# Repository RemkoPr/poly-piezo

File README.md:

# PolyPiezo

This repo contains the PCB design files for the wireless, modular, flexible piezoresistive skin sensor described in [Conveying Emotions to Robots through Touch and Sound](https://arxiv.org/abs/2412.03300), Qiaoqiao Ren, Remko Proesmans, et al, [Best Paper award at ICSR2024](https://icsr2024.dk/index.php/paper-nominees-and-awards/). Please contact remko.proesmans@ugent.be if you'd like support with implementing the design.

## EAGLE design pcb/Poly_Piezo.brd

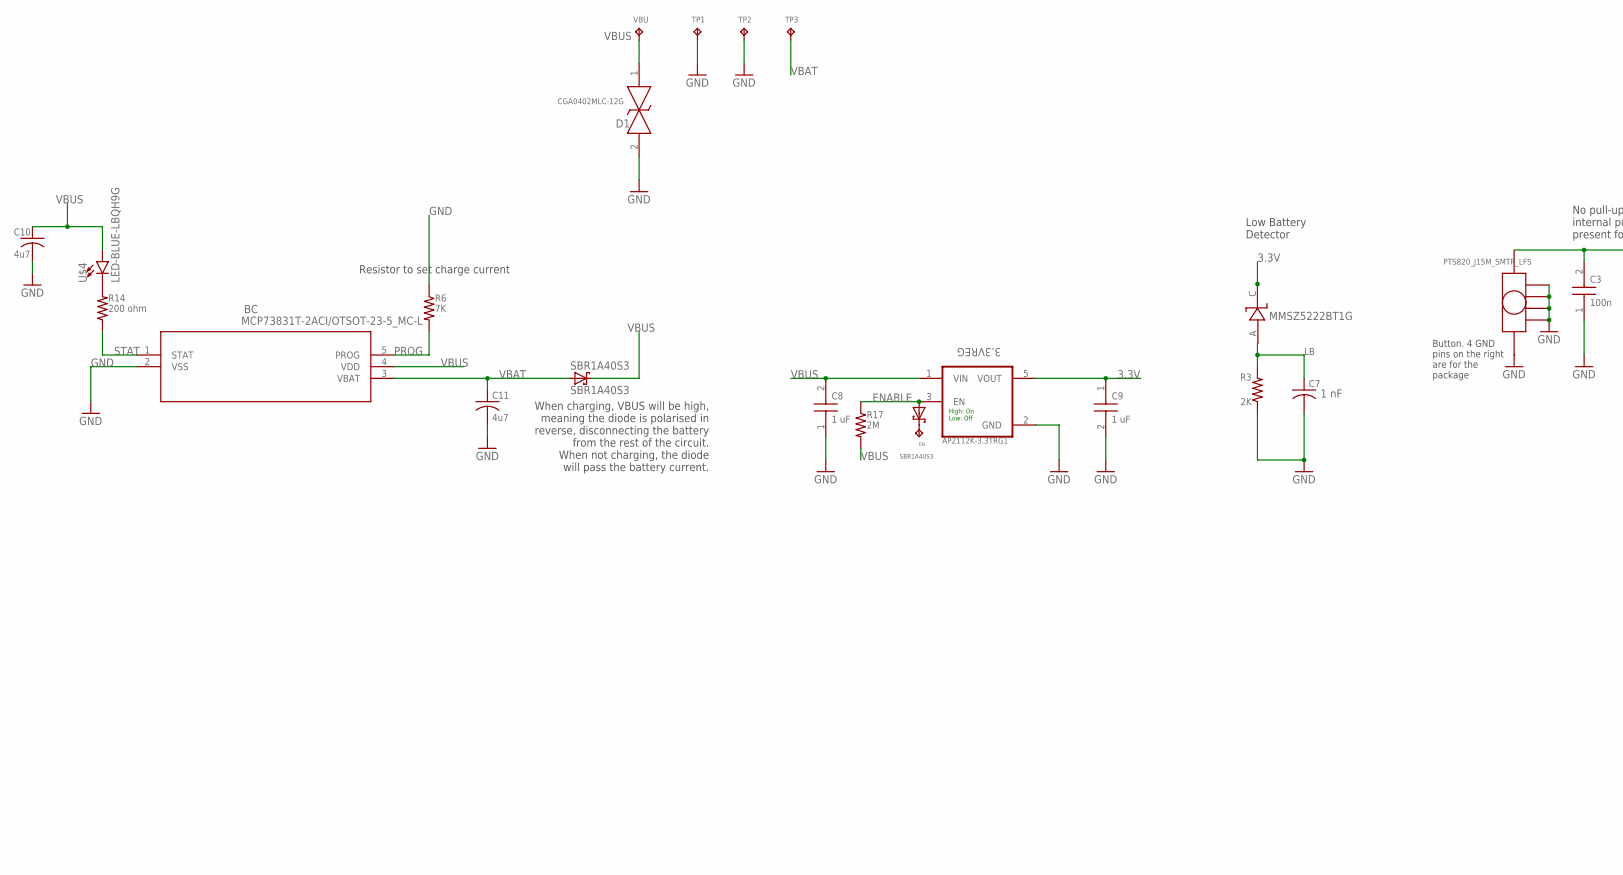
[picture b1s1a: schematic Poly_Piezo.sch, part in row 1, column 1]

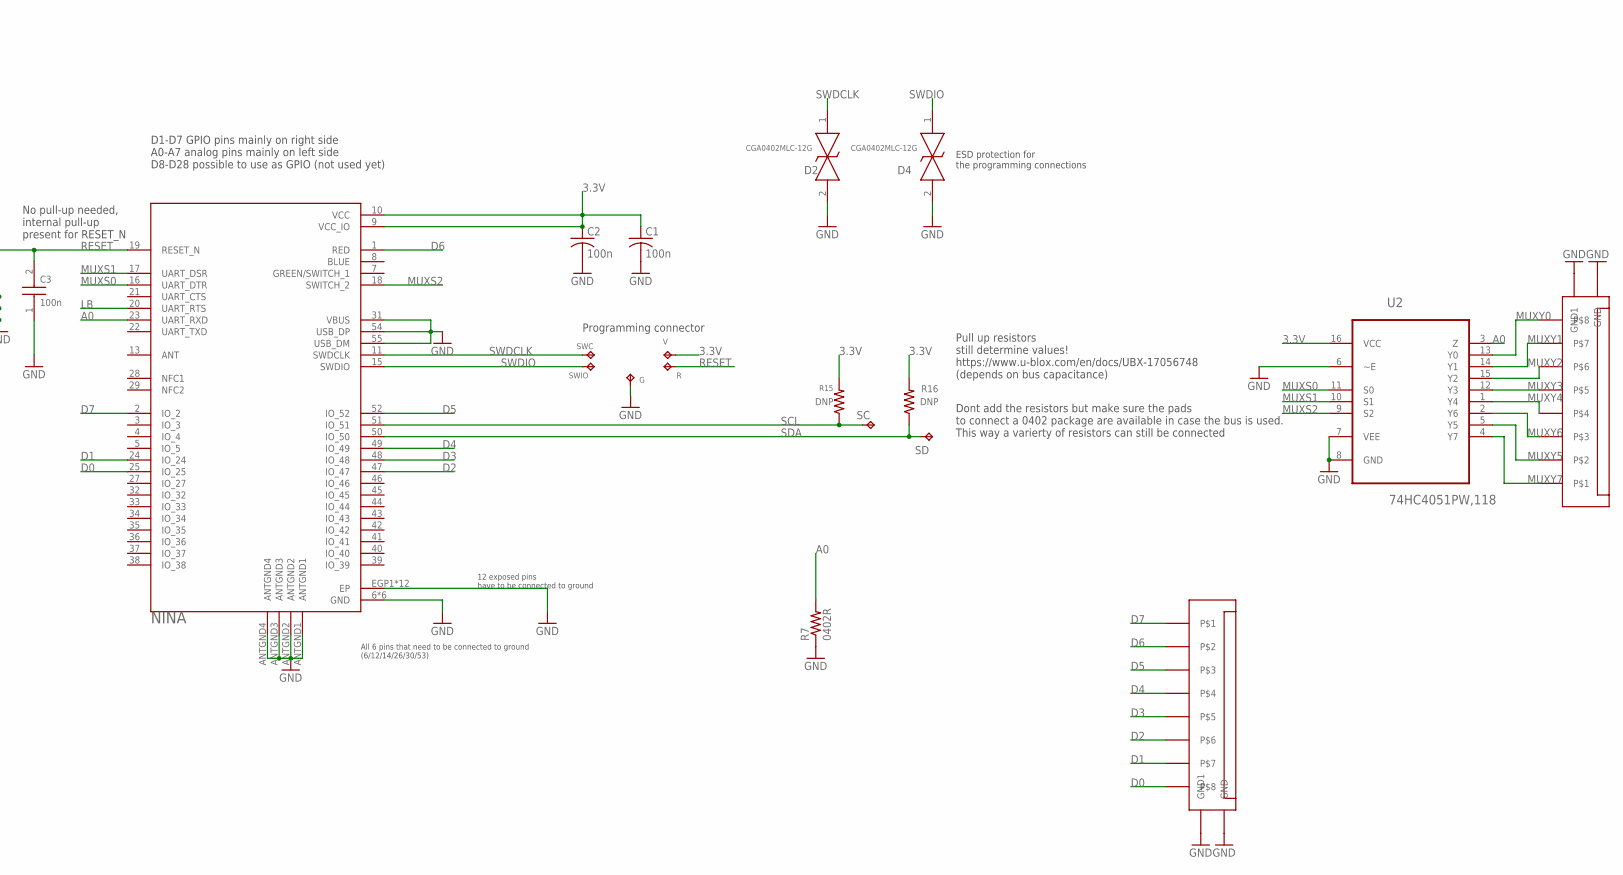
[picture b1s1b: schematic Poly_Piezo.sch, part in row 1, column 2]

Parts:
3.3VREG: AP2112K-3.3TRG1; SOT95P285X140-5N
BC: MCP73831T-2ACI/OTSOT-23-5_MC-L; SOT-23-5_MC-L
BUTTON: PTS820_J15M_SMTR_LFS; PTS820_J15
C1, C2: 100n; C0402
C3: 100n; CAPC1005X33N
C7: 1 nF; C0402
C8, C9: 1 uF; CAPC1005X33N
C10, C11: 4u7; C0402
D1, D2, D4: CGA0402MLC-12G; CGA0402MLC12G
EN: CUSTOM_HOLE1; CUSTOM_HOLE
G: TPB1,27; B1,27
MMSZ5222BT1G: MMSZ5222BT1G; SOD−123
R: TPB1,27; B1,27
R3: 2K; RESC1005X40N
R6: 7K; RESC1005X40N
R7: 0402R; RESC1005X40N
R14: 200 ohm; RESC1005X40N
R15, R16: DNP; RESC1005X40N
R17: 2M; RESC1005X40N
SBR1A40S3: SBR1A40S3; SOD323
SC: CUSTOM_HOLE1; CUSTOM_HOLE
SD: CUSTOM_HOLE1; CUSTOM_HOLE
SWC: TPB1,27; B1,27
SWIO: TPB1,27; B1,27
TP1, TP2, TP3: CUSTOM_HOLE1; CUSTOM_HOLE
U1: NINA; XCVR_NINA-B306
U2: 74HC4051PW,118; SOP65P640X110-16N
U$1, U$3: XF3M(1)-0815-1B
U$2: SBR1A40S3; SOD323
U$4: LED-BLUE-LBQH9G; LBQH9G-0402
V: TPB1,27; B1,27
VBU: CUSTOM_HOLE1; CUSTOM_HOLE

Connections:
3.3V: 3.3VREG.5 (VOUT), C1.1, C2.1, C9.1, MMSZ5222BT1G.C, R15.2, R16.2, U1.9 (VCC_IO), U1.10 (VCC), U2.16 (VCC), V.TP
A0: R7.2, U1.23 (UART_RXD), U2.3 (Z)
D0: U1.25 (IO_25), U$1.P$8
D1: U1.24 (IO_24), U$1.P$7
D2: U1.47 (IO_47), U$1.P$6
D3: U1.48 (IO_48), U$1.P$5
D4: U1.49 (IO_49), U$1.P$4
D5: U1.52 (IO_52), U$1.P$3
D6: U1.1 (RED), U$1.P$2
D7: U1.2 (IO_2), U$1.P$1
ENABLE: 3.3VREG.3 (EN), R17.1, U$2.A
GND: 3.3VREG.2 (GND), BC.2 (VSS), BUTTON.1, BUTTON.P$1, BUTTON.P$2, BUTTON.P$3, BUTTON.P$4, C1.2, C2.2, C3.1, C7.2, C8.1, C9.2, C10.2, C11.2, D1.2, D2.2, D4.2, G.TP, R3.1, R6.1, R7.1, TP1.P$1, TP2.P$1, U1.6 (GND), U1.12 (GND), U1.14 (GND), U1.26 (GND), U1.30 (GND), U1.31 (VBUS), U1.53 (GND), U1.54 (USB_DP), U1.55 (USB_DM), U1.ANTGND1, U1.ANTGND2, U1.ANTGND3, U1.ANTGND4, U1.EGP1 (EP), U1.EGP2 (EP), U1.EGP3 (EP), U1.EGP4 (EP), U1.EGP5 (EP), U1.EGP6 (EP), U1.EGP7 (EP), U1.EGP8 (EP), U1.EGP9 (EP), U1.EGP10 (EP), U1.EGP11 (EP), U1.EGP12 (EP), U2.6 (~E), U2.7 (VEE), U2.8 (GND), U$1.P$9 (GND1), U$1.P$10 (GND), U$3.P$9 (GND1), U$3.P$10 (GND)
LB: C7.1, MMSZ5222BT1G.A, R3.2, U1.20 (UART_RTS)
MUXS0: U1.16 (UART_DTR), U2.11 (S0)
MUXS1: U1.17 (UART_DSR), U2.10 (S1)
MUXS2: U1.18 (SWITCH_2), U2.9 (S2)
MUXY0: U2.13 (Y0), U$3.P$8
MUXY1: U2.14 (Y1), U$3.P$7
MUXY2: U2.15 (Y2), U$3.P$6
MUXY3: U2.12 (Y3), U$3.P$5
MUXY4: U2.1 (Y4), U$3.P$4
MUXY5: U2.5 (Y5), U$3.P$2
MUXY6: U2.2 (Y6), U$3.P$3
MUXY7: U2.4 (Y7), U$3.P$1
unnamed: R14.2, U$4.C
unnamed: EN.P$1, U$2.C
PROG: BC.5 (PROG), R6.2
RESET: BUTTON.2, C3.2, R.TP, U1.19 (RESET_N)
SCL: R15.1, SC.P$1, U1.51 (IO_51)
SDA: R16.1, SD.P$1, U1.50 (IO_50)
STAT: BC.1 (STAT), R14.1
SWDCLK: D2.1, SWC.TP, U1.11 (SWDCLK)
SWDIO: D4.1, SWIO.TP, U1.15 (SWDIO)
VBAT: BC.3 (VBAT), C11.1, SBR1A40S3.A, TP3.P$1
VBUS: 3.3VREG.1 (VIN), BC.4 (VDD), C8.2, C10.1, D1.1, R17.2, SBR1A40S3.C, U$4.A, VBU.P$1

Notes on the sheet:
Low Battery Detector
High: On Low: Off
When charging, VBUS will be high, meaning the diode is polarised in reverse, disconnecting the battery from the rest of the circuit. When not charging, the diode will pass the battery current.
Resistor to set charge current
D1-D7 GPIO pins mainly on right side A0-A7 analog pins mainly on left side D8-D28 possible to use as GPIO (not used yet)
12 exposed pins have to be connected to ground
All 6 pins that need to be connected to ground (6/12/14/26/30/53)
Pull up resistors still determine values! https://www.u-blox.com/en/docs/UBX-17056748 (depends on bus capacitance)
Dont add the resistors but make sure the pads to connect a 0402 package are available in case the bus is used. This way a varierty of resistors can still be connected
No pull-up needed, internal pull-up present for RESET_N
Programming connector
Button. 4 GND pins on the right are for the package
ESD protection for the programming connections

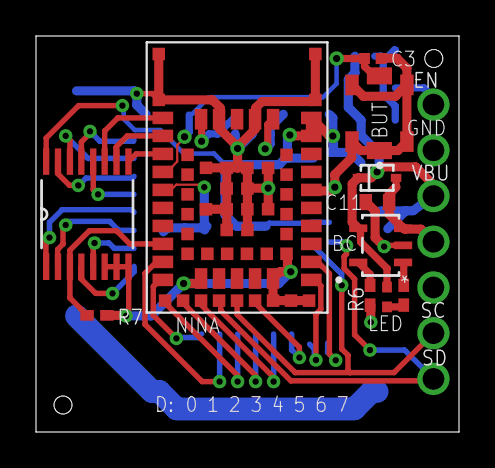
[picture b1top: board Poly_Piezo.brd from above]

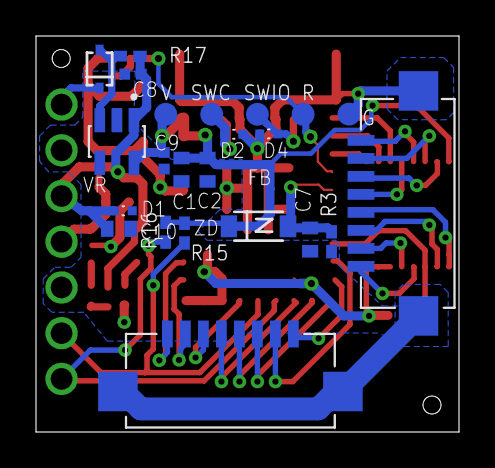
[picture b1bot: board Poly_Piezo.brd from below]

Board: 2 copper layers, 23.5 x 22.0 mm, 41 parts (24 on the bottom side), 35 nets.

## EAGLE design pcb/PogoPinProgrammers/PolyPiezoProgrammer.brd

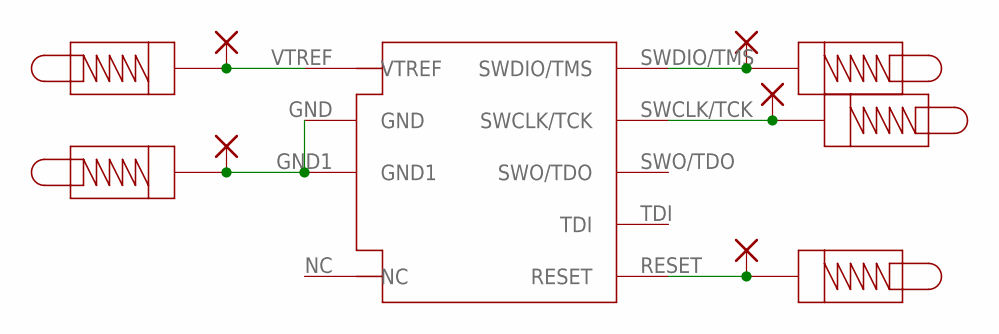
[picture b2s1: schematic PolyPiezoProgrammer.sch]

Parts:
PAD1, PAD2, PAD3, PAD4, PAD5: WIREPAD2,15/1,0; 2,15/1,0
U$1, U$2, U$3, U$4, U$5: 0930-0-15-20-75-14-11-0
U$6: JLINK_IF

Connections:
unnamed: PAD2.1, U$1.P$1, U$6.VTREF
unnamed: PAD1.1, U$2.P$1, U$6.GND, U$6.GND1
unnamed: PAD5.1, U$3.P$1, U$6.SWDIO/TMS
unnamed: PAD4.1, U$4.P$1, U$6.SWCLK/TCK
unnamed: PAD3.1, U$5.P$1, U$6.RESET

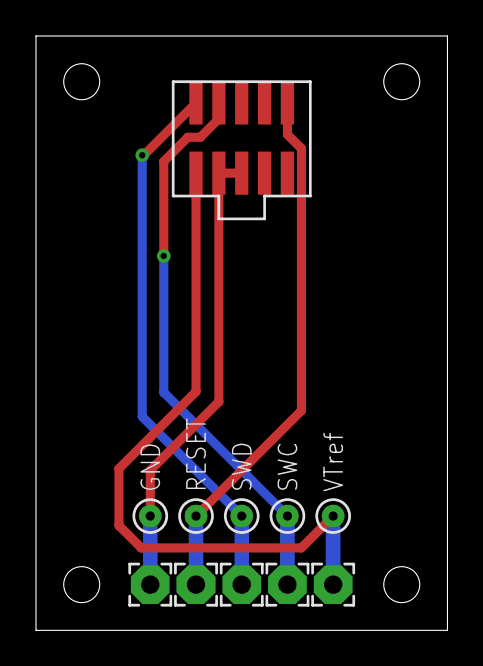
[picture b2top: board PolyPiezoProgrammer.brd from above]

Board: 2 copper layers, 22.9 x 33.0 mm, 11 parts (0 on the bottom side), 5 nets.

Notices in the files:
parts and their libraries:
SparkFun-LED: Licensing: Creative Commons ShareAlike 4.0 International - https://creativecommons.org/licenses/by-sa/4.0
